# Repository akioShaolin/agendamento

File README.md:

<h1>Projeto Injeção Programada</h1>
  <p>
    O projeto <strong>Injeção Programada</strong> tem como objetivo controlar a potência injetada por inversores fotovoltaicos através de comandos enviados por um microcontrolador <strong>ESP8266</strong> via comunicação <strong>RS485</strong>.
  </p>

  <h2>Descrição Geral</h2>
  <p>
    O sistema foi desenvolvido para integrar-se a inversores fotovoltaicos, permitindo limitar a potência de injeção conforme parâmetros definidos pelo usuário ou condições externas, como controle de demanda, compensação de energia, ou restrições impostas pela concessionária.
  </p>

  <h2>Funcionalidades Implementadas</h2>
  <ul>
    <li>Comunicação entre o <strong>ESP8266</strong> e o inversor via <strong>RS485</strong>.</li>
    <li>Envio de comandos Modbus RTU para ajuste da potência ativa injetada.</li>
    <li>Leitura de registradores do inversor para monitoramento de status e potência.</li>
    <li>Estrutura modular do código em <code>Arduino</code>, com separação entre comunicação, controle e interface.</li>
    <li>Função de temporização para atualização periódica dos comandos.</li>
    <li>Tratamento de erros de comunicação e reconexão automática do barramento.</li>
  </ul>

  <h2>Tecnologias Utilizadas</h2>
  <ul>
    <li><strong>ESP8266</strong> — microcontrolador principal.</li>
    <li><strong>RS485</strong> — interface de comunicação industrial entre dispositivos.</li>
    <li><strong>Modbus RTU</strong> — protocolo de comunicação com o inversor.</li>
    <li><strong>Arduino IDE</strong> — ambiente de desenvolvimento.</li>
  </ul>

  <h2>Próximos Passos</h2>
  <ul>
    <li>Implementar controle dinâmico baseado em sensores externos (corrente, potência ou sinal da rede).</li>
    <li>Adicionar interface web para configuração remota via Wi-Fi.</li>
    <li>Registrar logs de operação e eventos de falha.</li>
  </ul>

  <p>
    Para mais detalhes técnicos e histórico de desenvolvimento, consulte os registros e discussões do projeto.
  </p>

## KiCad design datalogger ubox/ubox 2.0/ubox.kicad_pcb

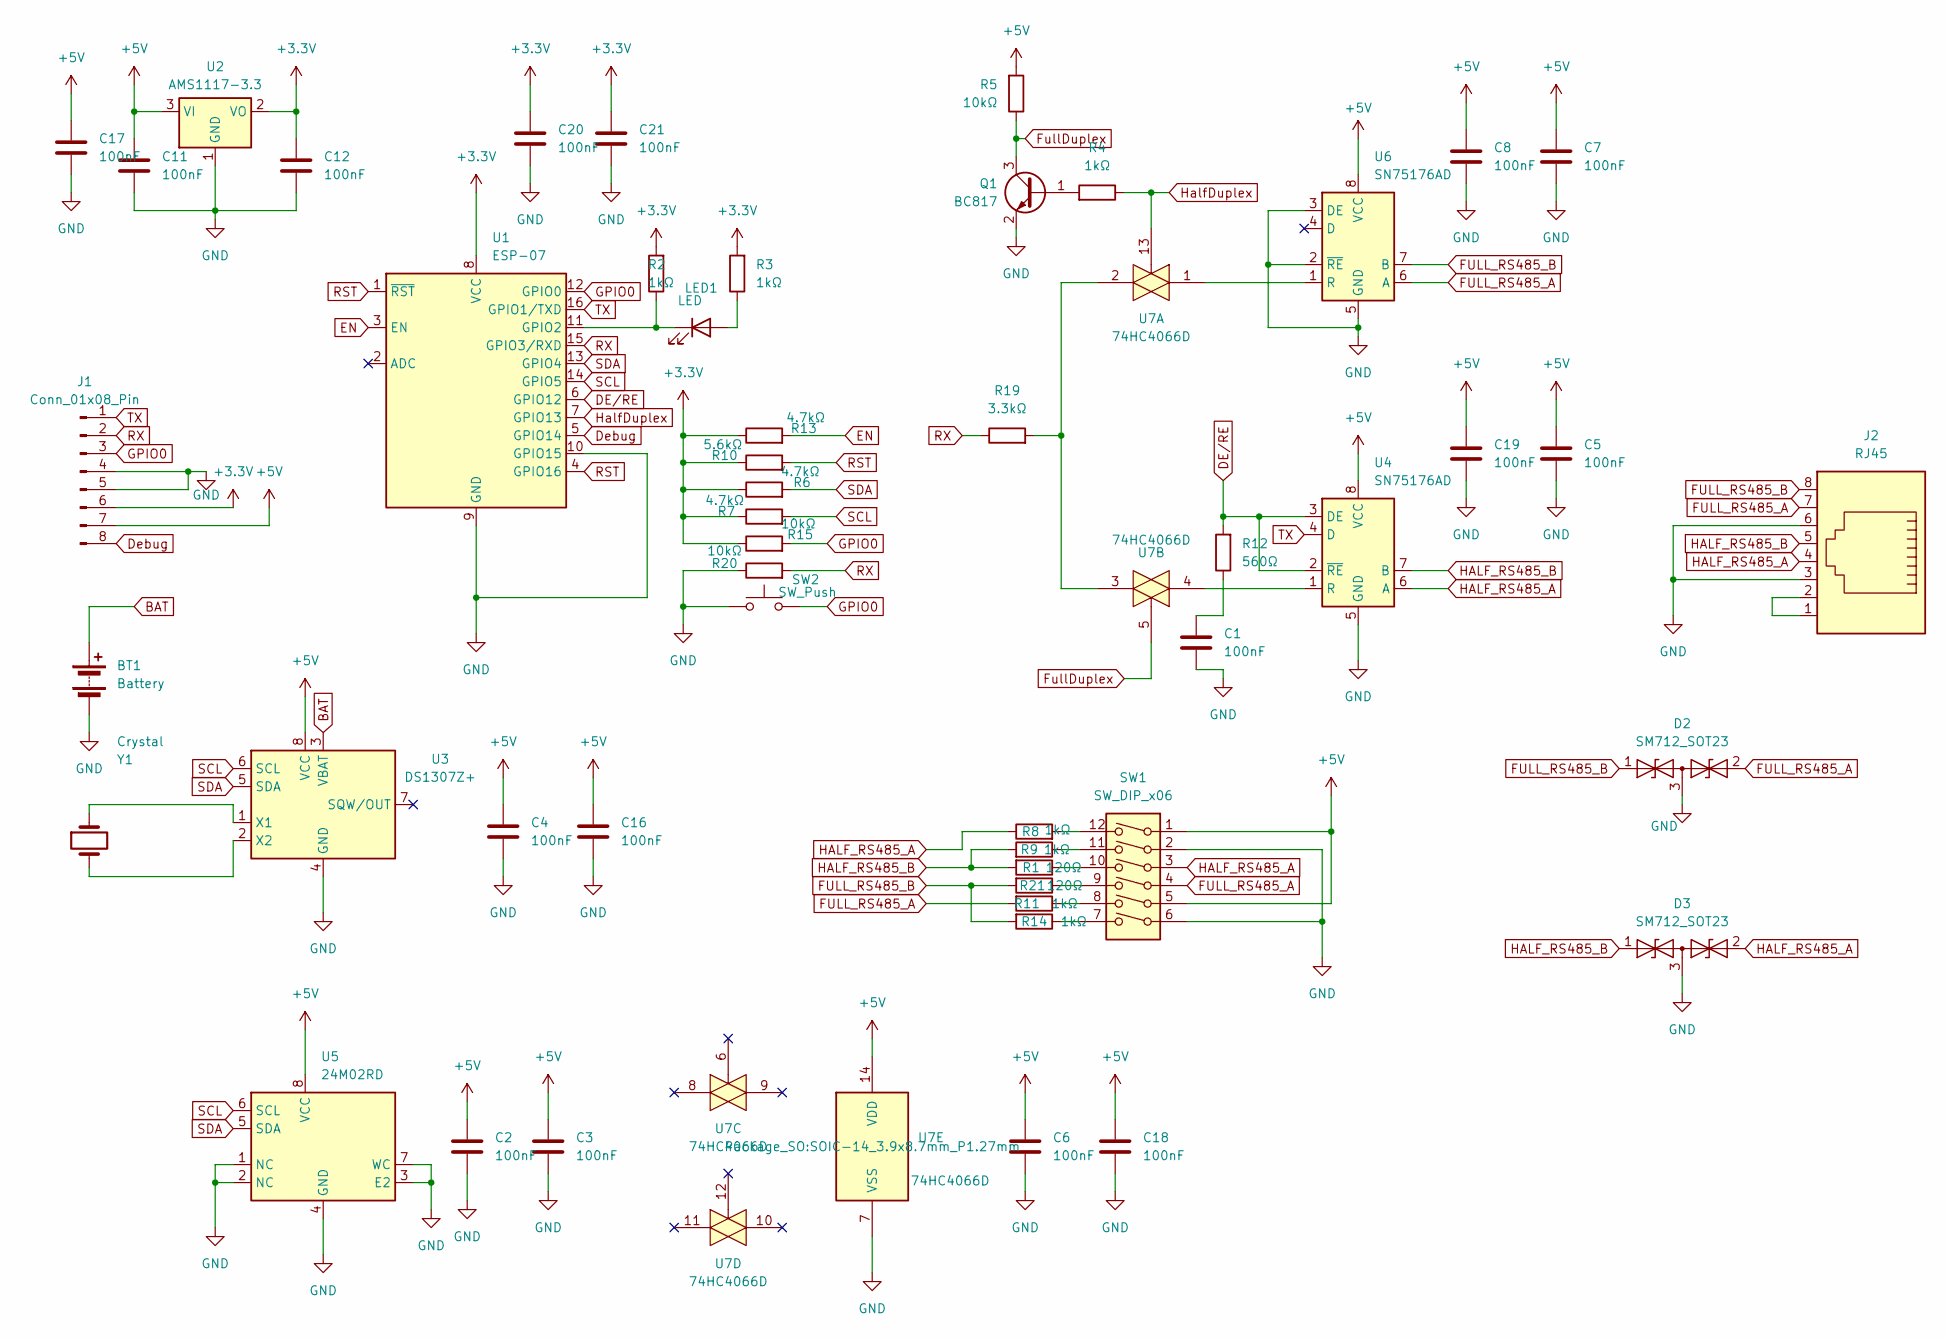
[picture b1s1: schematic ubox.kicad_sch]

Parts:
BT1: Battery; BatteryHolder_LINX_BAT-HLD-012-SMT
C1, C3, C4, C6, C8, C19, C20: 100nF; C_0603_1608Metric
C2, C5, C7, C11, C12, C16, C17, C18, C21: 100nF; C_0805_2012Metric
D2, D3: SM712_SOT23; SOT-23
J1: Conn_01x08_Pin; PinHeader_1x08_P2.00mm_Vertical
J2: RJ45; RJ45_Amphenol_54602-x08_Horizontal
LED1: LED; LED_0805_2012Metric
Q1: BC817; SOT-23
R1, R21: 120Ω; R_0603_1608Metric
R2, R3, R4, R11, R14: 1kΩ; R_0603_1608Metric
R5, R15, R20: 10kΩ; R_0603_1608Metric
R6, R7, R13: 4.7kΩ; R_0603_1608Metric
R8, R9: 1kΩ; R_0805_2012Metric
R10: 5.6kΩ; R_0603_1608Metric
R12: 560Ω; R_0603_1608Metric
R19: 3.3kΩ; R_0603_1608Metric
SW1: SW_DIP_x06; SW_DIP_SPSTx06_Slide_9.78x17.42mm_W7.62mm_P2.54mm
SW2: SW_Push; SW_SPST_Omron_B3F-315x_Angled
U1: ESP-07
U2: AMS1117-3.3; SOT-223-3_TabPin2
U3: DS1307Z+; SOIC-8_3.9x4.9mm_P1.27mm
U4, U6: SN75176AD; SOIC-8_3.9x4.9mm_P1.27mm
U5: 24M02RD; SOIC-8_3.9x4.9mm_P1.27mm
U7: 74HC4066D; SOIC-14_3.9x8.7mm_P1.27mm
Y1: Crystal; Crystal_DS26_D2.0mm_L6.0mm_Horizontal

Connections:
+3.3V: C12.1, C20.1, C21.1, J1.6, R2.2, R3.2, R6.1, R7.1, R10.1, R13.1, R15.1, U1.8 (VCC), U2.2 (VO)
+5V: C2.1, C3.1, C4.1, C5.1, C6.1, C7.1, C8.1, C11.1, C16.1, C17.1, C18.1, C19.1, J1.7, R5.2, SW1.1, SW1.5, U2.3 (VI), U3.8 (VCC), U4.8 (VCC), U5.8 (VCC), U6.8 (VCC), U7.14 (VDD)
BAT: BT1.1 (+), U3.3 (VBAT)
DE/RE: R12.2, U1.6 (GPIO12), U4.2 (~RE), U4.3 (DE)
Debug: J1.8, U1.5 (GPIO14)
EN: R13.2, U1.3 (EN)
FULL_RS485_A: D2.2 (A2), J2.7, R11.2, SW1.4, U6.6 (A)
FULL_RS485_B: D2.1 (A1), J2.8, R14.2, R21.2, U6.7 (B)
FullDuplex: Q1.3 (C), R5.1, U7.5
GND: BT1.2 (-), C1.2, C2.2, C3.2, C4.2, C5.2, C6.2, C7.2, C8.2, C11.2, C12.2, C16.2, C17.2, C18.2, C19.2, C20.2, C21.2, D2.3 (common), D3.3 (common), J1.4, J1.5, J2.3, J2.6, Q1.2 (E), R20.1, SW1.2, SW1.6, SW2.2, U1.9 (GND), U1.10 (GPIO15), U2.1 (GND), U3.4 (GND), U4.5 (GND), U5.1 (NC), U5.2 (NC), U5.3 (E2), U5.4 (GND), U5.7 (WC), U6.2 (~RE), U6.3 (DE), U6.5 (GND), U7.7 (VSS)
GPIO0: J1.3, R15.2, SW2.1, U1.12 (GPIO0)
HALF_RS485_A: D3.2 (A2), J2.4, R8.1, SW1.3, U4.6 (A)
HALF_RS485_B: D3.1 (A1), J2.5, R1.2, R9.2, U4.7 (B)
HalfDuplex: R4.1, U1.7 (GPIO13), U7.13
unnamed: C1.1, R12.1
unnamed: J2.1, J2.2
unnamed: LED1.2 (A), R3.1
unnamed: LED1.1 (K), R2.1, U1.11 (GPIO2)
unnamed: Q1.1 (B), R4.2
unnamed: R1.1, SW1.10
unnamed: R8.2, SW1.12
unnamed: R9.1, SW1.11
unnamed: R11.1, SW1.8
unnamed: R14.1, SW1.7
unnamed: R19.2, U7.2, U7.3
unnamed: R21.1, SW1.9
unnamed: U3.1 (X1), Y1.1
unnamed: U3.2 (X2), Y1.2
unnamed: U4.1 (R), U7.4
unnamed: U6.1 (R), U7.1
RST: R10.2, U1.1 (~RST), U1.4 (GPIO16)
RX: J1.2, R19.1, R20.2, U1.15 (GPIO3/RXD)
SCL: R7.2, U1.14 (GPIO5), U3.6 (SCL), U5.6 (SCL)
SDA: R6.2, U1.13 (GPIO4), U3.5 (SDA), U5.5 (SDA)
TX: J1.1, U1.16 (GPIO1/TXD), U4.4 (D)

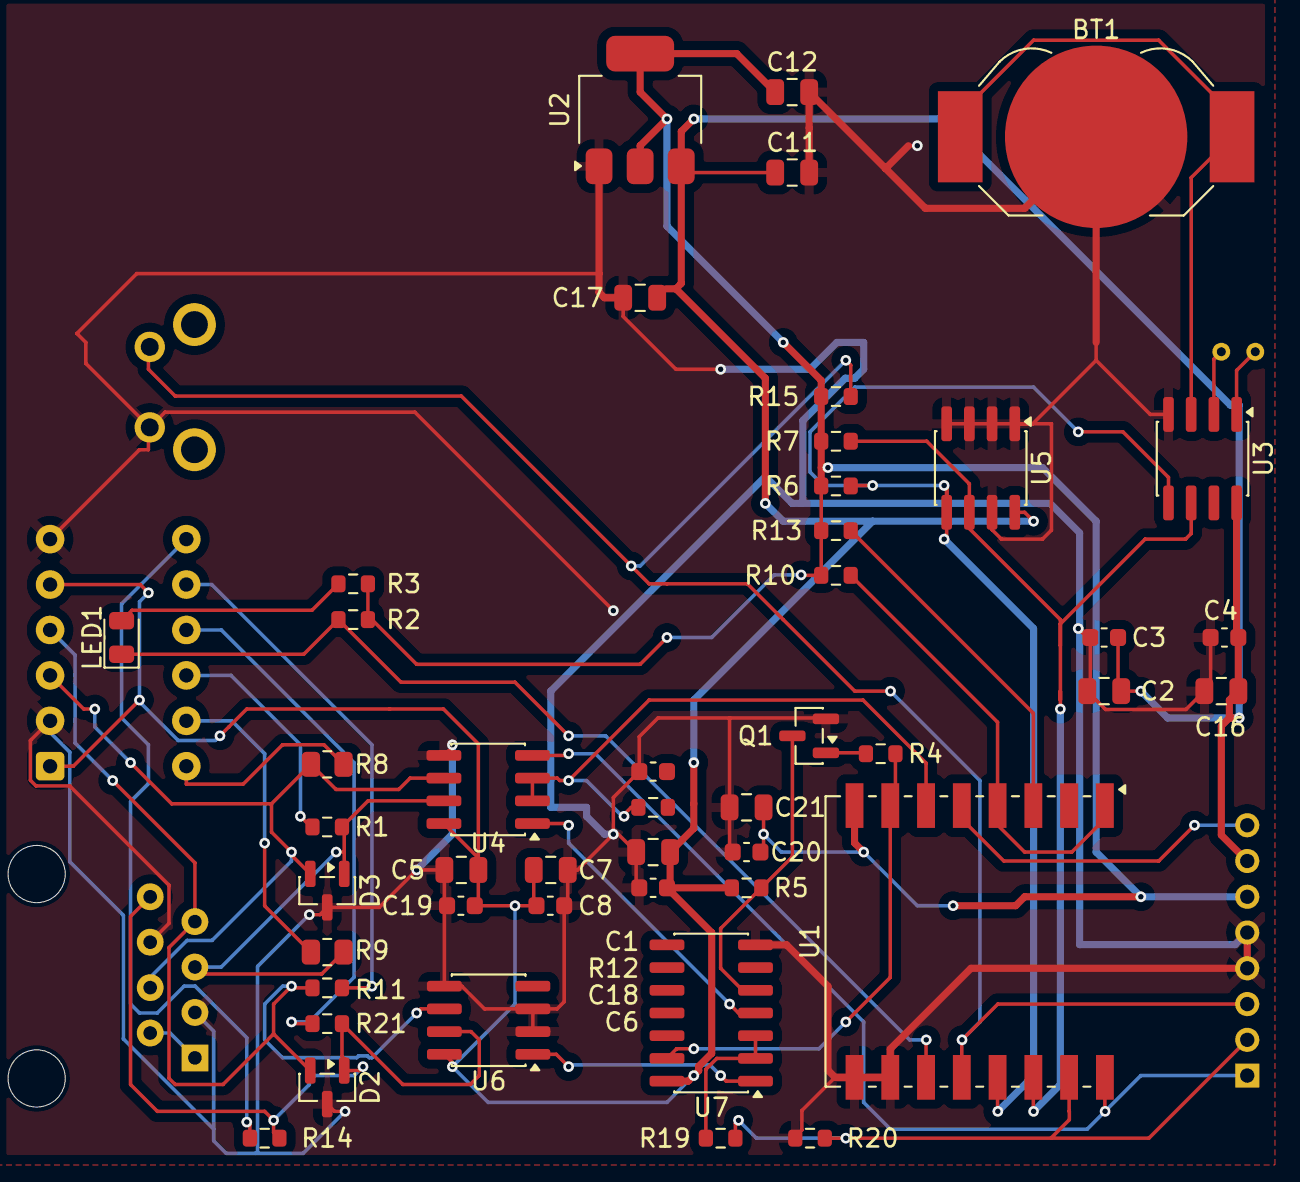
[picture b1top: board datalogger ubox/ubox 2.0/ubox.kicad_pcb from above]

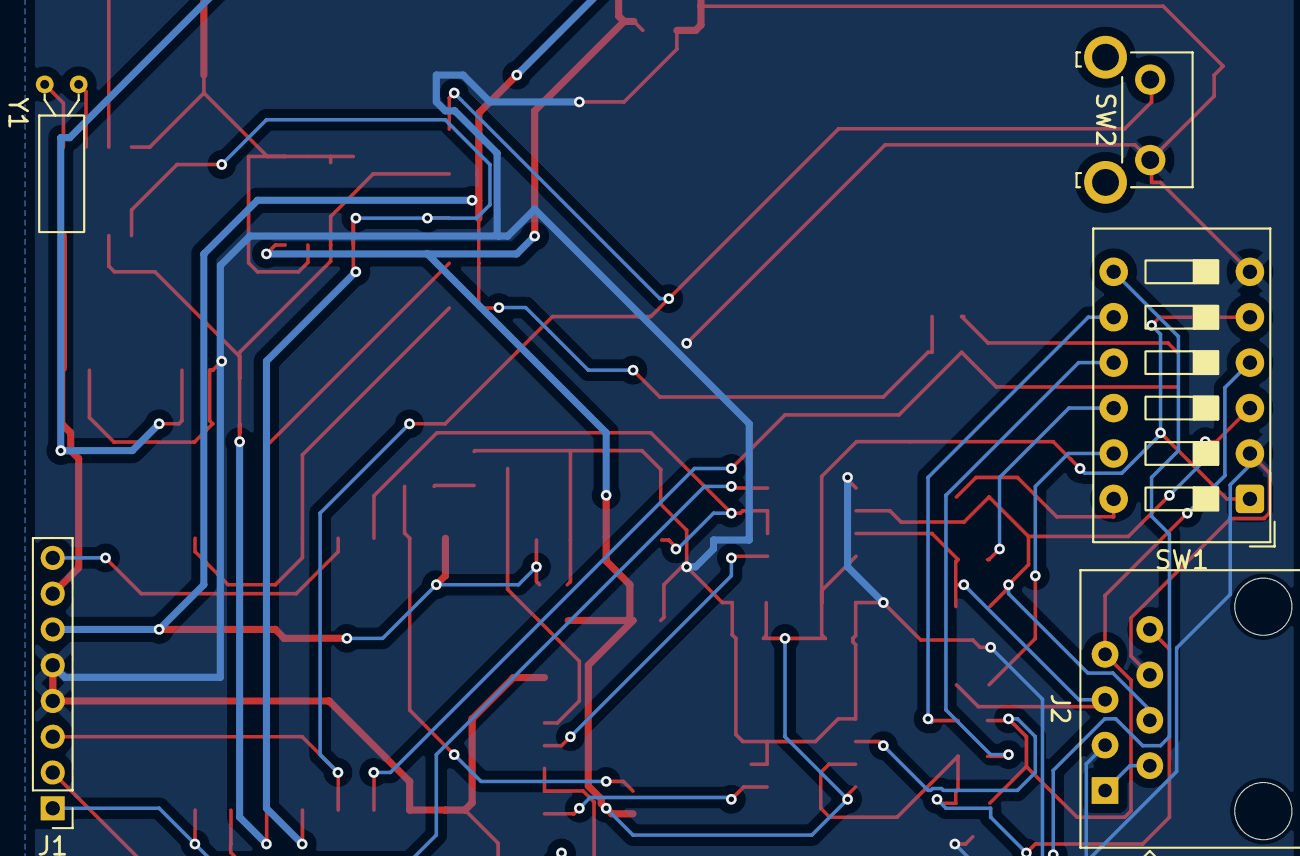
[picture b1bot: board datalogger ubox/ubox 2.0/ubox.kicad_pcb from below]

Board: 2 copper layers, 51 parts (5 on the bottom side), 35 nets.

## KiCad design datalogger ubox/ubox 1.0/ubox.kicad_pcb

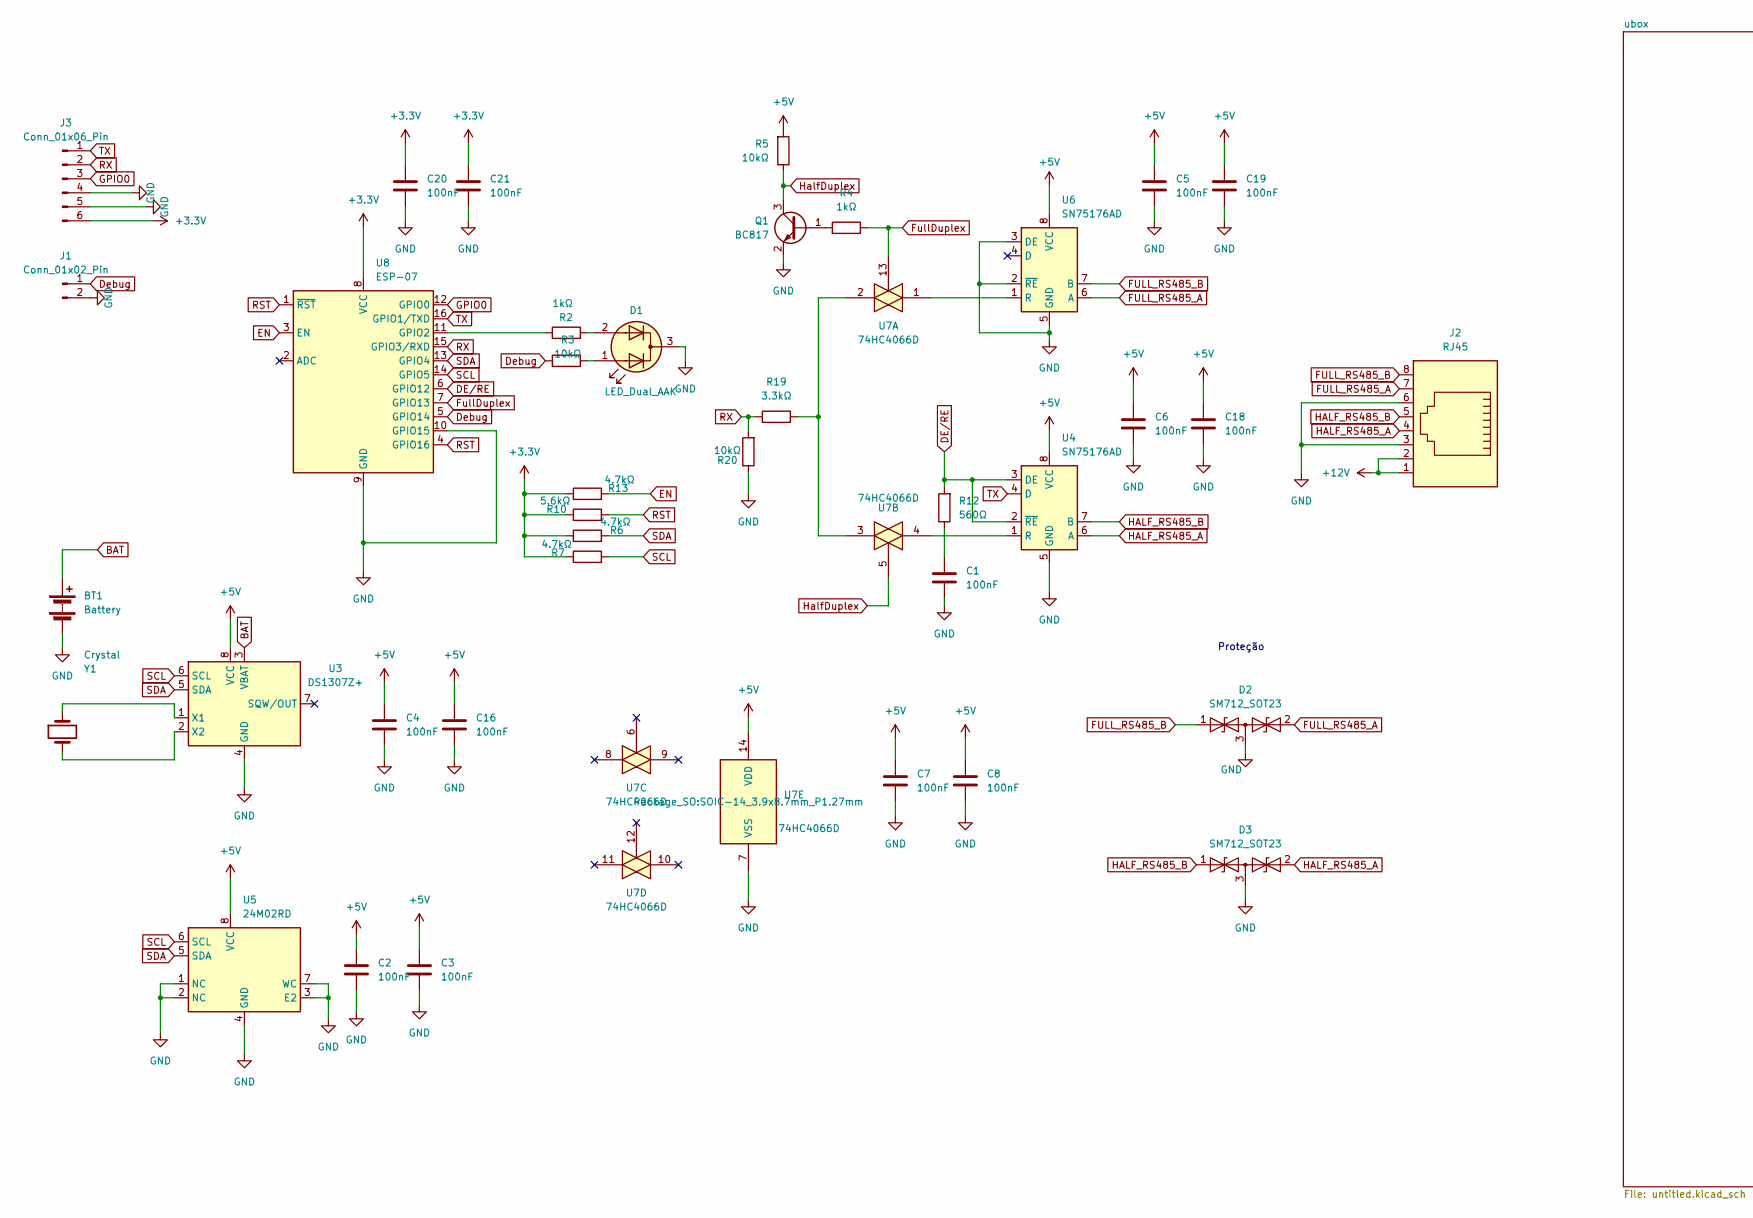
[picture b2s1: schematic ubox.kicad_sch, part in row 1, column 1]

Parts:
BT1: Battery; BatteryHolder_LINX_BAT-HLD-012-SMT
C1, C2, C3, C4, C5, C6, C8, C16, C18, C19, C20, C21: 100nF; C_0805_2012Metric
C7: 100nF; R_0805_2012Metric
D1: LED_Dual_AAK; LED_D3.0mm-3
D2, D3: SM712_SOT23; SOT-23
J1: Conn_01x02_Pin; PinHeader_1x02_P2.54mm_Vertical
J2: RJ45; RJ45_Amphenol_54602-x08_Horizontal
J3: Conn_01x06_Pin; PinHeader_1x06_P2.54mm_Vertical
Q1: BC817; SOT-23
R2, R4: 1kΩ; R_0805_2012Metric
R3, R5: 10kΩ; R_0805_2012Metric
R6, R7, R13: 4.7kΩ; R_0805_2012Metric
R10: 5.6kΩ; R_0805_2012Metric
R12: 560Ω; R_0805_2012Metric
R19: 3.3kΩ; R_0603_1608Metric
R20: 10kΩ; R_0603_1608Metric
U3: DS1307Z+; SOIC-8_3.9x4.9mm_P1.27mm
U4, U6: SN75176AD; SOIC-8_3.9x4.9mm_P1.27mm
U5: 24M02RD; SOIC-8_3.9x4.9mm_P1.27mm
U7: 74HC4066D; SOIC-14_3.9x8.7mm_P1.27mm
U8: ESP-07
Y1: Crystal; Crystal_DS26_D2.0mm_L6.0mm_Vertical

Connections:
+3.3V: C20.1, C21.1, J3.6, R6.1, R7.1, R10.1, R13.1, U8.8 (VCC); also elsewhere on the board
+5V: C2.1, C3.1, C4.1, C5.1, C6.1, C7.1, C8.1, C16.1, C18.1, C19.1, R5.2, U3.8 (VCC), U4.8 (VCC), U5.8 (VCC), U6.8 (VCC), U7.14 (VDD); also elsewhere on the board
+12V: J2.1, J2.2; also elsewhere on the board
BAT: BT1.1 (+), U3.3 (VBAT)
DE/RE: R12.2, U4.2 (~RE), U4.3 (DE), U8.6 (GPIO12)
Debug: J1.1, R3.1, U8.5 (GPIO14)
EN: R13.2, U8.3 (EN)
FULL_RS485_A: D2.2 (A2), J2.7, U6.6 (A)
FULL_RS485_B: D2.1 (A1), J2.8, U6.7 (B)
FullDuplex: R4.1, U7.13, U8.7 (GPIO13)
GND: BT1.2 (-), C1.2, C2.2, C3.2, C4.2, C5.2, C6.2, C7.2, C8.2, C16.2, C18.2, C19.2, C20.2, C21.2, D1.3 (K), D2.3 (common), D3.3 (common), J1.2, J2.3, J2.6, J3.4, J3.5, Q1.2 (E), R20.1, U3.4 (GND), U4.5 (GND), U5.1 (NC), U5.2 (NC), U5.3 (E2), U5.4 (GND), U5.7 (WC), U6.2 (~RE), U6.3 (DE), U6.5 (GND), U7.7 (VSS), U8.9 (GND), U8.10 (GPIO15); also elsewhere on the board
GPIO0: J3.3, U8.12 (GPIO0)
HALF_RS485_A: D3.2 (A2), J2.4, U4.6 (A)
HALF_RS485_B: D3.1 (A1), J2.5, U4.7 (B)
HalfDuplex: Q1.3 (C), R5.1, U7.5
unnamed: C1.1, R12.1
unnamed: D1.1 (A1), R3.2
unnamed: D1.2 (A2), R2.2
unnamed: Q1.1 (B), R4.2
unnamed: R19.2, U7.2, U7.3
unnamed: U3.1 (X1), Y1.1
unnamed: U3.2 (X2), Y1.2
unnamed: U4.1 (R), U7.4
unnamed: U6.1 (R), U7.1
unnamed: R2.1, U8.11 (GPIO2)
RST: R10.2, U8.1 (~RST), U8.4 (GPIO16)
RX: J3.2, R19.1, R20.2, U8.15 (GPIO3/RXD)
SCL: R7.2, U3.6 (SCL), U5.6 (SCL), U8.14 (GPIO5)
SDA: R6.2, U3.5 (SDA), U5.5 (SDA), U8.13 (GPIO4)
TX: J3.1, U4.4 (D), U8.16 (GPIO1/TXD)

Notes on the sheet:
Proteção

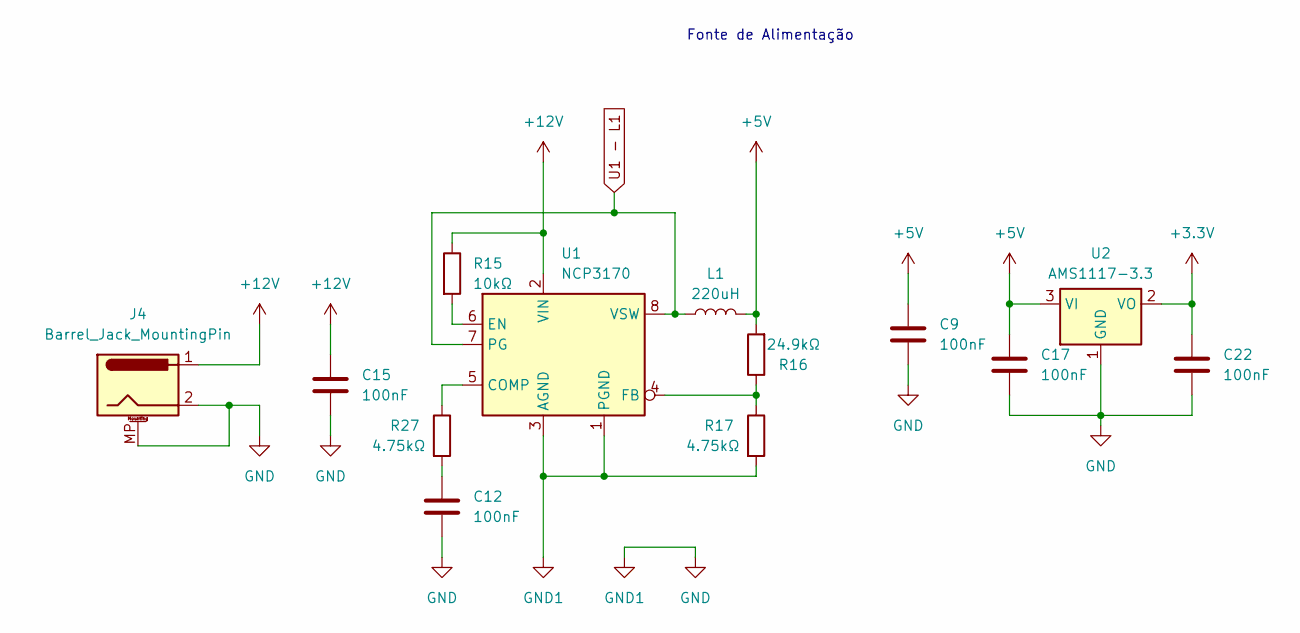
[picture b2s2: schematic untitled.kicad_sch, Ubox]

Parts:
C9, C12, C15, C17, C22: 100nF; C_0805_2012Metric
J4: Barrel_Jack_MountingPin; BarrelJack_Horizontal
L1: 220uH; L_Coilcraft_XAL7030-222
R15: 10kΩ; R_0805_2012Metric
R16: 24.9kΩ; R_0805_2012Metric
R17, R27: 4.75kΩ; R_0805_2012Metric
U1: NCP3170; SOIC-8_3.9x4.9mm_P1.27mm
U2: AMS1117-3.3; SOT-223-3_TabPin2

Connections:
+3.3V: C22.1, U2.2 (VO); also elsewhere on the board
+5V: C9.1, C17.1, L1.2, R16.2, U2.3 (VI); also elsewhere on the board
+12V: C15.1, J4.1, R15.1, U1.2 (VIN); also elsewhere on the board
GND: C9.2, C12.2, C15.2, C17.2, C22.2, J4.2, J4.MP (MountPin), R17.2, U1.1 (PGND), U1.3 (AGND), U2.1 (GND); also elsewhere on the board
unnamed: C12.1, R27.2
unnamed: R27.1, U1.5 (COMP)
unnamed: R15.2, U1.6 (EN)
unnamed: R16.1, R17.1, U1.4 (FB)
U1 - L1: L1.1, U1.7 (PG), U1.8 (VSW)

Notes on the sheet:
Fonte de Alimentação

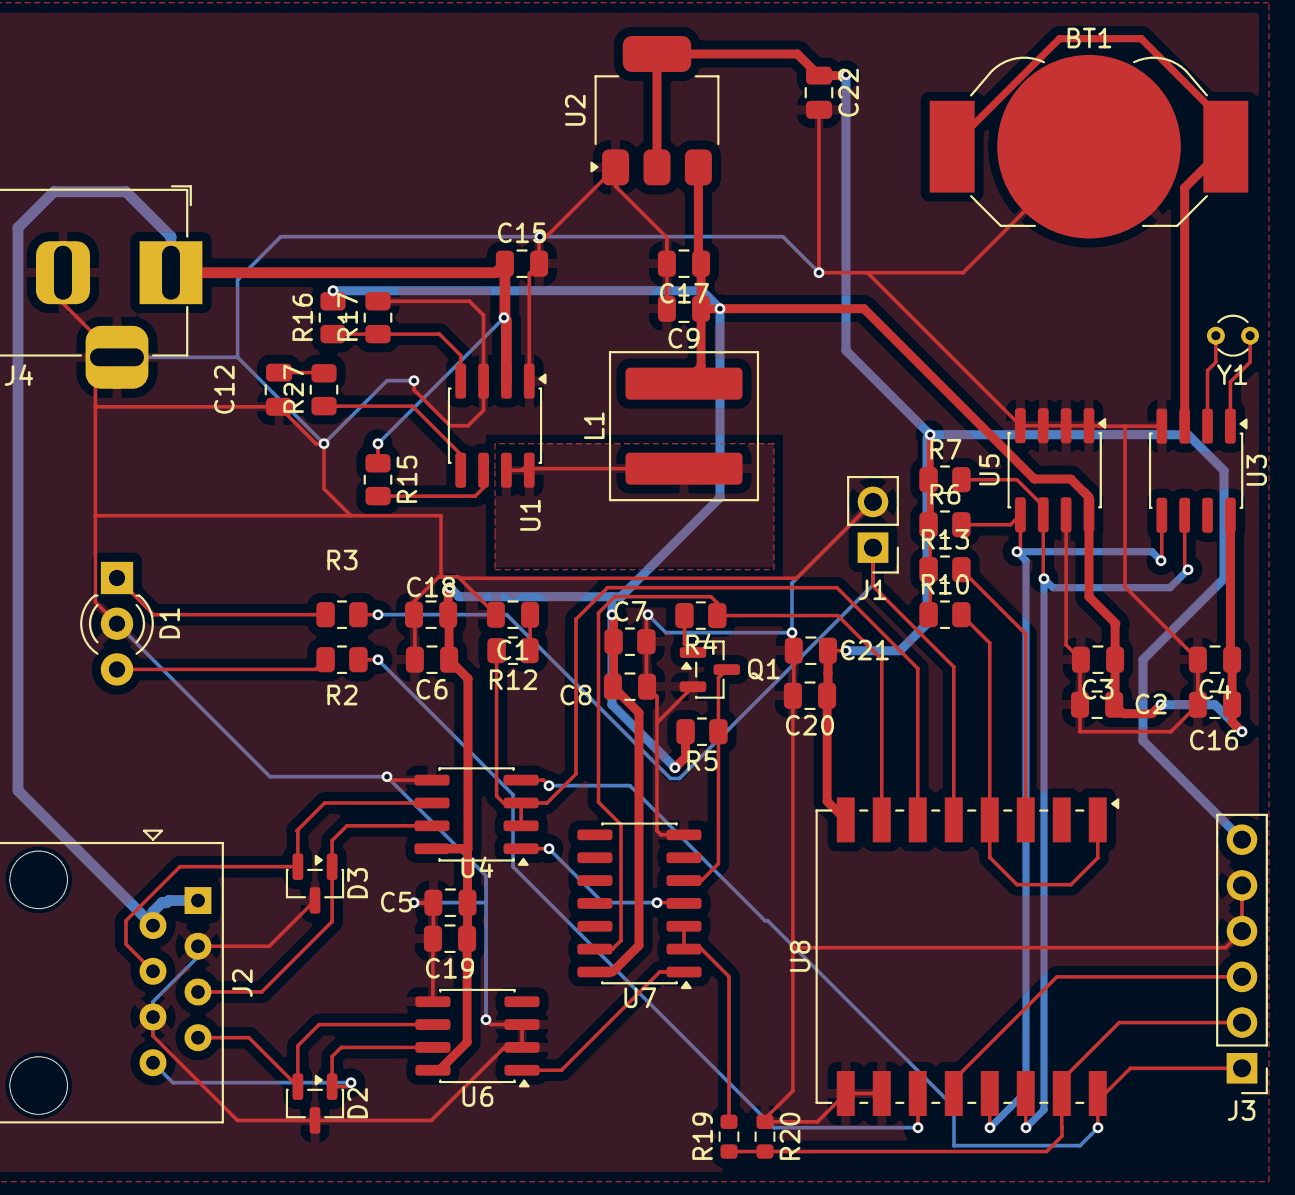
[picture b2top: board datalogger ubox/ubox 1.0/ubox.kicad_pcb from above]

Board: 2 copper layers, 52 parts (0 on the bottom side), 35 nets.

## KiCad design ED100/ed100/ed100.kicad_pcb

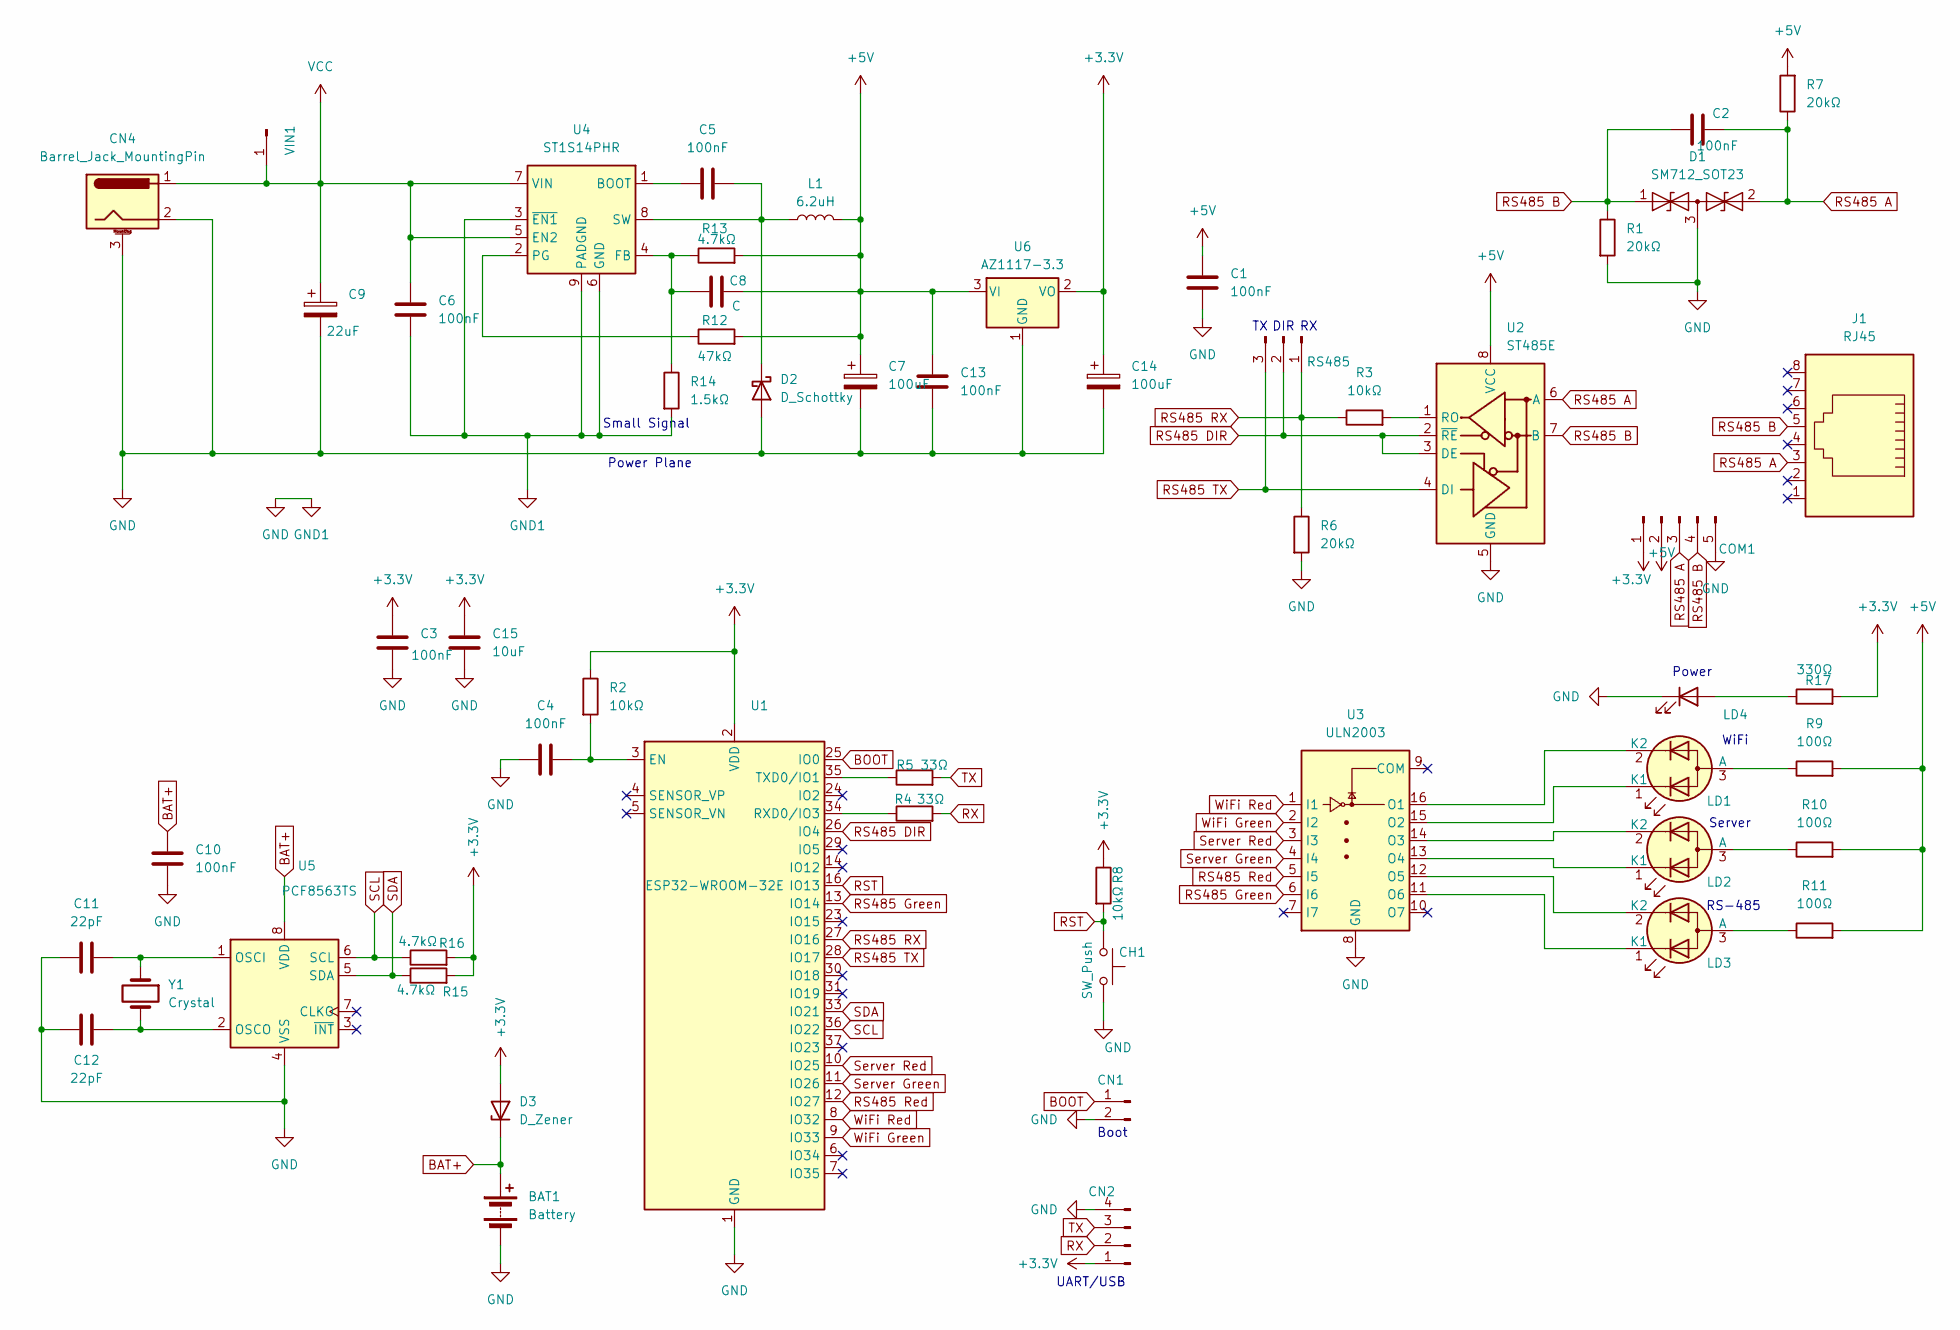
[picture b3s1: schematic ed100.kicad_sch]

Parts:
BAT1: Battery; BatteryHolder_MPD_BC2003_1x2032
C1, C2, C3, C4, C5, C6, C10, C13: 100nF; C_0603_1608Metric
C7, C14: 100uF; C_Elec_4x5.4
C8: C; C_0603_1608Metric
C9: 22uF; C_Elec_6.3x5.4
C11, C12: 22pF; C_0603_1608Metric
C15: 10uF; C_0603_1608Metric
CH1: SW_Push; SW_SPST_Omron_B3F-315x_Angled
CN1: Conn_01x02_Pin; PinHeader_1x02_P2.54mm_Vertical
CN2: Conn_01x04_Pin; PinHeader_1x04_P2.54mm_Vertical
CN4: Barrel_Jack_MountingPin; BarrelJack_Horizontal
COM1: Conn_01x05_Pin; PinHeader_1x05_P2.54mm_Vertical
D1: SM712_SOT23; SOT-23
D2: D_Schottky; D_SMB
D3: D_Zener; D_SOD-123
J1: RJ45; RJ45_Amphenol_54602-x08_Horizontal
L1: 6.2uH; L_SOREDE_SNR.1050_10x10x5mm
LD1, LD2, LD3: LED_Dual_KKA; LED_D3.0mm-3
LD4: LED; LED_D3.0mm
R1, R6, R7: 20kΩ; R_0603_1608Metric
R2, R3, R8: 10kΩ; R_0603_1608Metric
R4, R5: 33Ω; R_0805_2012Metric
R9, R10, R11: 100Ω; R_0805_2012Metric
R12: 47kΩ; R_0603_1608Metric
R13, R15, R16: 4.7kΩ; R_0603_1608Metric
R14: 1.5kΩ; R_0603_1608Metric
R17: 330Ω; R_0805_2012Metric
RS485: Conn_01x03_Pin; PinHeader_1x03_P2.54mm_Vertical
U1: ESP32-WROOM-32E; ESP32-WROOM-32D
U2: ST485E; SOIC-8_3.9x4.9mm_P1.27mm
U3: ULN2003; SO-16_3.9x9.9mm_P1.27mm
U4: ST1S14PHR; TI_SO-PowerPAD-8
U5: PCF8563TS; MSOP-8_3x3mm_P0.65mm
U6: AZ1117-3.3; SOT-223-3_TabPin2
VIN1: Conn_01x01_Pin; PinHeader_1x01_P2.54mm_Vertical
Y1: Crystal; Crystal_SMD_3215-2Pin_3.2x1.5mm

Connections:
+3.3V: C3.1, C14.1, C15.1, CN2.1, COM1.1, D3.2 (A), R2.1, R8.1, R15.2, R16.2, R17.2, U1.2 (VDD), U6.2 (VO)
+5V: C1.1, C7.1, C8.2, C13.1, COM1.2, L1.2, R7.2, R9.2, R10.2, R11.2, R12.2, R13.2, U2.8 (VCC), U6.3 (VI)
BAT+: BAT1.1 (+), C10.1, D3.1 (K), U5.8 (VDD)
BOOT: CN1.1, U1.25 (IO0)
GND: BAT1.2 (-), C1.2, C3.2, C4.2, C6.2, C7.2, C9.2, C10.2, C11.2, C12.2, C13.2, C14.2, C15.2, CH1.2, CN1.2, CN2.4, CN4.2, CN4.3 (MountPin), COM1.5, D1.3 (common), D2.2 (A), LD4.1 (K), R1.2, R6.2, R14.2, U1.1 (GND), U1.15 (GND), U1.38 (GND), U1.39 (GND), U2.5 (GND), U3.8 (GND), U4.3 (~EN1), U4.6 (GND), U4.9 (PADGND), U5.4 (VSS), U6.1 (GND)
unnamed: C5.2, D2.1 (K), L1.1, U4.8 (SW)
unnamed: LD1.3 (A), R9.1
unnamed: LD1.1 (K1), U3.15 (O2)
unnamed: LD1.2 (K2), U3.16 (O1)
unnamed: LD2.3 (A), R10.1
unnamed: LD2.1 (K1), U3.13 (O4)
unnamed: LD2.2 (K2), U3.14 (O3)
unnamed: LD3.3 (A), R11.1
unnamed: LD3.1 (K1), U3.11 (O6)
unnamed: LD3.2 (K2), U3.12 (O5)
unnamed: LD4.2 (A), R17.1
unnamed: C4.1, R2.2, U1.3 (EN)
unnamed: R4.1, U1.34 (RXD0/IO3)
unnamed: R5.1, U1.35 (TXD0/IO1)
unnamed: R3.2, U2.1 (RO)
unnamed: C5.1, U4.1 (BOOT)
unnamed: C8.1, R13.1, R14.1, U4.4 (FB)
unnamed: R12.1, U4.2 (PG)
unnamed: C11.1, U5.1 (OSCI), Y1.1
unnamed: C12.1, U5.2 (OSCO), Y1.2
RS485 A: C2.2, COM1.3, D1.2 (A2), J1.3, R7.1, U2.6 (A)
RS485 B: C2.1, COM1.4, D1.1 (A1), J1.5, R1.1, U2.7 (B)
RS485 DIR: RS485.2, U1.26 (IO4), U2.2 (~RE), U2.3 (DE)
RS485 Green: U1.13 (IO14), U3.6 (I6)
RS485 RX: R3.1, R6.1, RS485.1, U1.27 (IO16)
RS485 Red: U1.12 (IO27), U3.5 (I5)
RS485 TX: RS485.3, U1.28 (IO17), U2.4 (DI)
RST: CH1.1, R8.2, U1.16 (IO13)
RX: CN2.2, R4.2
SCL: R16.1, U1.36 (IO22), U5.6 (SCL)
SDA: R15.1, U1.33 (IO21), U5.5 (SDA)
Server Green: U1.11 (IO26), U3.4 (I4)
Server Red: U1.10 (IO25), U3.3 (I3)
TX: CN2.3, R5.2
VCC: C6.1, C9.1, CN4.1, U4.5 (EN2), U4.7 (VIN), VIN1.1
WiFi Green: U1.9 (IO33), U3.2 (I2)
WiFi Red: U1.8 (IO32), U3.1 (I1)

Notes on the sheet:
Power
RS-485
UART/USB
Boot
Server
WiFi
Power Plane
DIR
Small Signal

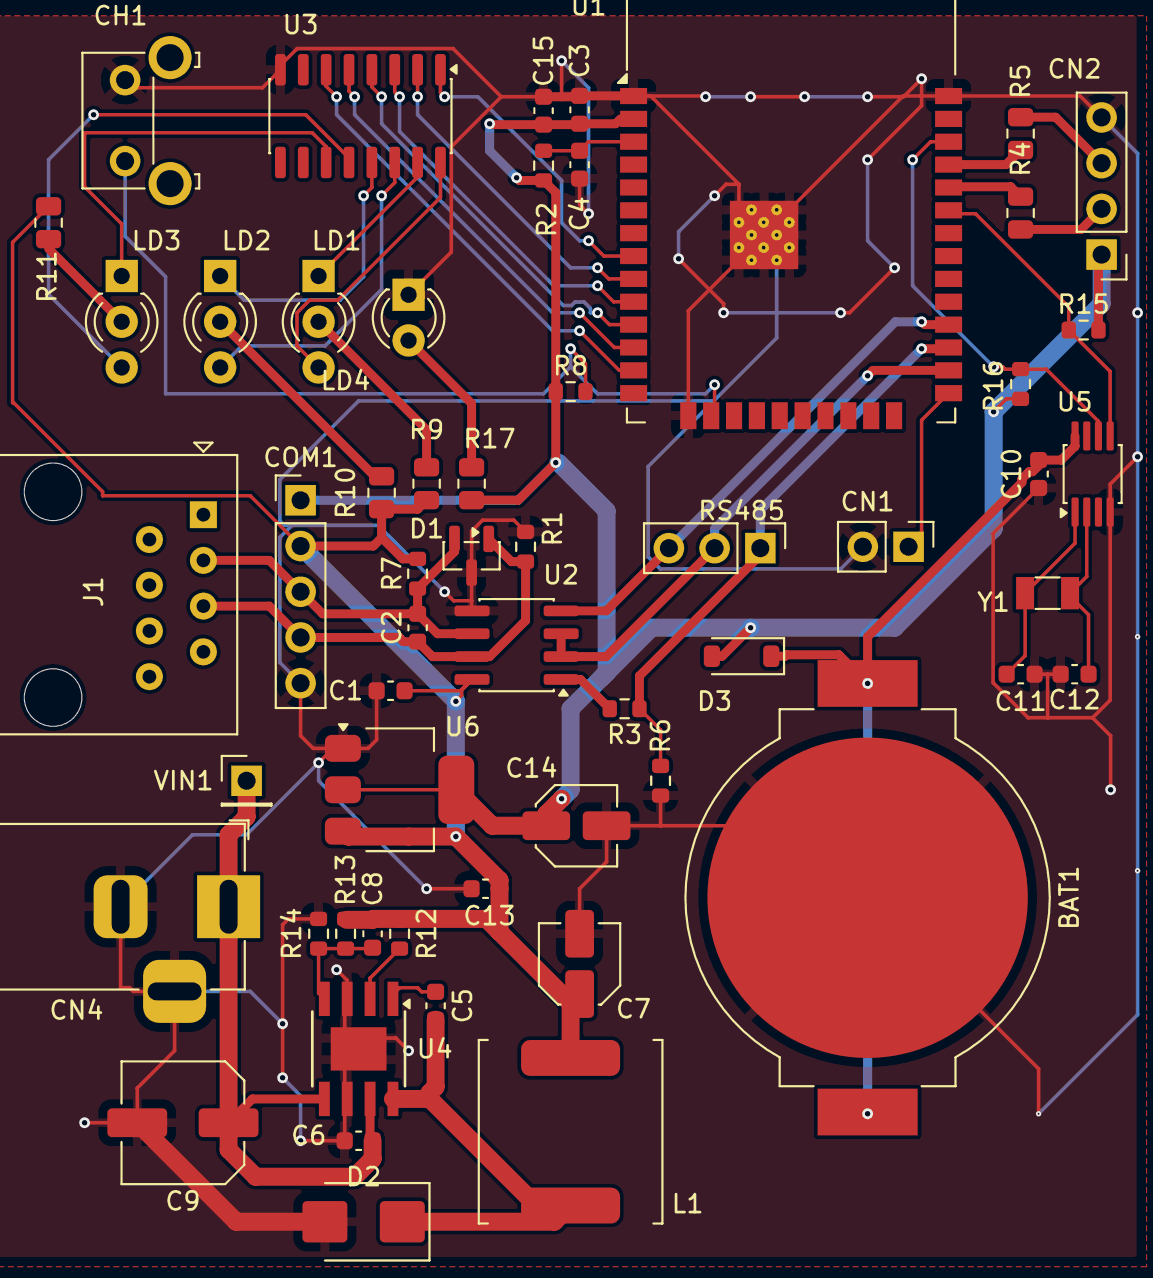
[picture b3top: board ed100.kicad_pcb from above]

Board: 2 copper layers, 56 parts (0 on the bottom side), 42 nets.

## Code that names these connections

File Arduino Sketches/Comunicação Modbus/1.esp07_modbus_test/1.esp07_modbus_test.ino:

#include <ModbusRTU.h>

// --- Configurações dos pinos ---
// Mapeamento de pinos do NodeMCU ESP8266 (para referência)
// D0 = GPIO16
// D1 = GPIO5
// D2 = GPIO4
// D3 = GPIO0
// D4 = GPIO2
// D5 = GPIO14
// D6 = GPIO12
// D7 = GPIO13
// D8 = GPIO15
// RX = GPIO3
// TX = GPIO1

#define SLAVE_ID 1       // ID do dispositivo escravo que queremos ler
#define REG_ADDR 40301     // Endereço do primeiro registrador a ser lido
#define REG_COUNT 10      // Quantidade de registradores a ler
#define CTRL_PIN 12      // Pino do ESP8266 conectado ao DE/RE do 75176B (GPIO12)

ModbusRTU mb; // Cria o objeto ModbusRTU

// Buffer para armazenar os registradores lidos
uint16_t holdingRegisters[REG_COUNT];

// Callback para tratar as respostas Modbus
// Esta função será chamada pela biblioteca quando uma resposta for recebida ou um erro ocorrer
// A assinatura correta para o callback é bool (*)(Modbus::ResultCode, uint16_t, void*)
// Baseado no exemplo master.ino da biblioteca
bool read_cb(Modbus::ResultCode event, uint16_t transactionId, void* data) {
  if (event == Modbus::EX_SUCCESS) {
    Serial.printf("Resposta recebida! ID da Transação: %d, Sucesso.\n", transactionId);
    // Os dados já foram escritos no array 'holdingRegisters' pela função readHreg
    for (int i = 0; i < REG_COUNT; i++) {
      Serial.printf("  - Registrador %d: %d\n", REG_ADDR + i, holdingRegisters[i]);
    }
  } else {
    Serial.printf("Resposta recebida! ID da Transação: %d, Erro: 0x%X\n", transactionId, event);
  }
  Serial.println("--------------------");
  return true; // Retorna true para que a biblioteca continue processando
}

void setup() {
  Serial.begin(9600); // Inicia a serial para debug no monitor

  delay(2000);

  Serial.println("Iniciando Mestre Modbus RTU...");

  // Inicia a comunicação Modbus na porta Serial principal (TX/RX)
  // A 9600 bps, 8 bits de dados, sem paridade, 1 stop bit (padrão)
  // E informa que o pino CTRL_PIN será usado para controle de direção (DE/RE)
  mb.begin(&Serial, CTRL_PIN); 
  
  // Define o ESP8266 como mestre
  mb.master();
}

void loop() {
  // A função task() deve ser chamada em cada ciclo do loop.
  // Ela gerencia o estado da comunicação, envia solicitações na fila e processa respostas.
  mb.task();

  // Envia uma solicitação de leitura a cada 5 segundos, apenas se não houver uma transação pendente
  static unsigned long lastRequestTime = 0;
  // A função isTransaction() retorna true se há uma transação em andamento
  if (millis() - lastRequestTime > 5000 && !mb.isTransaction()) {
    lastRequestTime = millis();c:\Users\pedro.sakuma\Downloads\modbus-esp8266-master.zip
    
    Serial.println("Enviando solicitação de leitura...");
    
    // Coloca uma solicitação de leitura na fila.
    // mb.readHreg(ID_ESCRAVO, ENDEREÇO_INICIAL, PONTEIRO_PARA_ARRAY_DE_DADOS, QUANTIDADE_DE_REGISTRADORES, CALLBACK_DA_RESPOSTA);
    // A função retorna um ID de transação, que pode ser usado para rastrear a solicitação.
    uint16_t transactionId = mb.readHreg(SLAVE_ID, REG_ADDR, holdingRegisters, REG_COUNT, read_cb);

    if (transactionId == 0) {
      Serial.println("Falha ao enviar solicitação. A fila pode estar cheia ou parâmetros inválidos.");
    } else {
      Serial.printf("Solicitação enviada com ID de Transação: %d\n", transactionId);
    }
  }
}

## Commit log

2025-10-24 Add initial README for Injeção Programada project
    This README provides an overview of the 'Injeção Programada' project, detailing its objectives, functionalities, technologies used, and future steps.
2025-10-29 Sincronização 29102025
2025-12-19 Atualização de esquemas eletrônicos, testes utilizando o ED100 com ESP32
2026-02-10 Atualização do Gateway Modbus e inicio dos estucos com MQQT
2026-02-17 Alterações no firmware 4.0, scanner modbus e Agendamento DO com CC100
2026-02-20 Leitura do DTSU666 via modbus RTU e TCP usando ESP8266 e python
